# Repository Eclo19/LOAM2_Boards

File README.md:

# LOAM2_Boards_Winter/Spring_2026

## Description
These files contain the progress done on drone hardware for the LOAM 2 project. The current strategy is to produce a support board that connects to the Pixhawk's FMU, communicates with the nodes, and hosts many other vital systems. This board should concentrate as many of the drone peripherals as possible in a single PCB to ensure robustness. The support board contains the following sub-systems:

 * Power management and battery monitoring (PM)
 * GPS
 * ARM Switch
 * nRF54L15 (MCU)
 * nRF21540 (FEM)
 * GPS patch antenna
 * Bluetooth antenna (not certain yet)
 * JST Connectors for the FMU harness
 * Debug taps for all outputs

## Power Management

The power management issue is mostly solved. The board stored in `power_management_tests` was produced and thoroughly tested. We confirmed its outputs were the expected 3.3 and 5V, it handled the throuttle of the drone motors, and voltage and current readings are in agreement with lab equipment. **Note:** To ensure proper voltage and current readings, the resistor ratios implemented in the voltage and current sensors must be taken into account by the software. In Ardupilot, simply set `BATT_VOLT_MULT = 5.667` and `BATT_AMP_PERVLT = 25.0`. The chosen buck-converters can output currents of up to 3 A, far more than the FMU or the support board systems might draw. 

When redoing the layout for this board in the support board, make sure to follow IC datasheet recommendations and lay thick traces in the battery input and output ports, which can draw large currents (~80 A). 

## GPS

The GPS schematics were adapted from this repository: https://github.com/ZIOCC/Zio-Qwiic-GPS-Module-U-blox-NEO-M8N-0-10). They leverage the NEO-M8N-0 chip and a patch antenna at the GPS band of 1575.42 MHz. 

## Arm Switch

This replaces the floating ARM switch in the Pixhawk. 

## MCU and FEM

The drone communicates with node sensors through the nRF54L15 MCU using BLE. Currently, we assume the nodes will also host this MCU, as inter-communication between this IC is simple. The MCU is powered by the 3.3 V power line produced by the PM. Communication with the FMU is done through the TELEM2 port, which connects through UART to pins on the suppoart board MCU. 

The current drone wake-up strategy is to rely on energy harvesting to charge the base of an $npn$ transistor (2N3904) above its $V_{th}$, flipping the collector voltage from 3.3 V to 0 when charged, thus waking up the node. The node MCU must handle this and a few nuances regarding oscillation (described in our report) in firmware. We used the AEM30940 DK for our energy harvesting tests on the chosen band of 2.45 GHz. To ensure enough energy can be transmitted to charge the base of the transistor to around 0.65 V, a decent amount of power must be received. The The 47 C.F.R. § 15.247 permits a maximum of 1 W (30 dBm) of transmission power for the 2.45 GHz band given a few constraints, and the nRF54L15 can ony output a maximum of 8 dBm. To increase transmission power, we connect an RF FEM, the nRF21540, a bidirectional FEM (LNA for Rx and PA for Tx, with shiwtching controlled by GPIO pins or SPI). The antenna choice is still a major question for this transmission. 

The drone MCU in the suppoart board is programmed through an SWD interface. 

## Connectors and Debug Taps

The support board hosts multiple connectors that should be tightly packed in a harness connected to the FMU. These include the following ports: GPS, TELEM2, SWITCH, and POWER. Our initial connector selection was a DF13, but these are not fully compatible. We believe the correct connectors are JST. For testing and debugging reasons, it is helpful to pack debup taps for many essential nodes in the system (e.g. 3V3, 5V, CURRENT_SENSE, RX_GPS, etc). 

## Layout Notes

The layout of the support board has just started at the time of this README.md file. Like in the power management test board, the support board has DRCs from JLC PCB, imported from https://github.com/sethhillbrand/kicad_templates/tree/master. This board has 4 layers though, as opposed to the simple 2-layer power management tests board.

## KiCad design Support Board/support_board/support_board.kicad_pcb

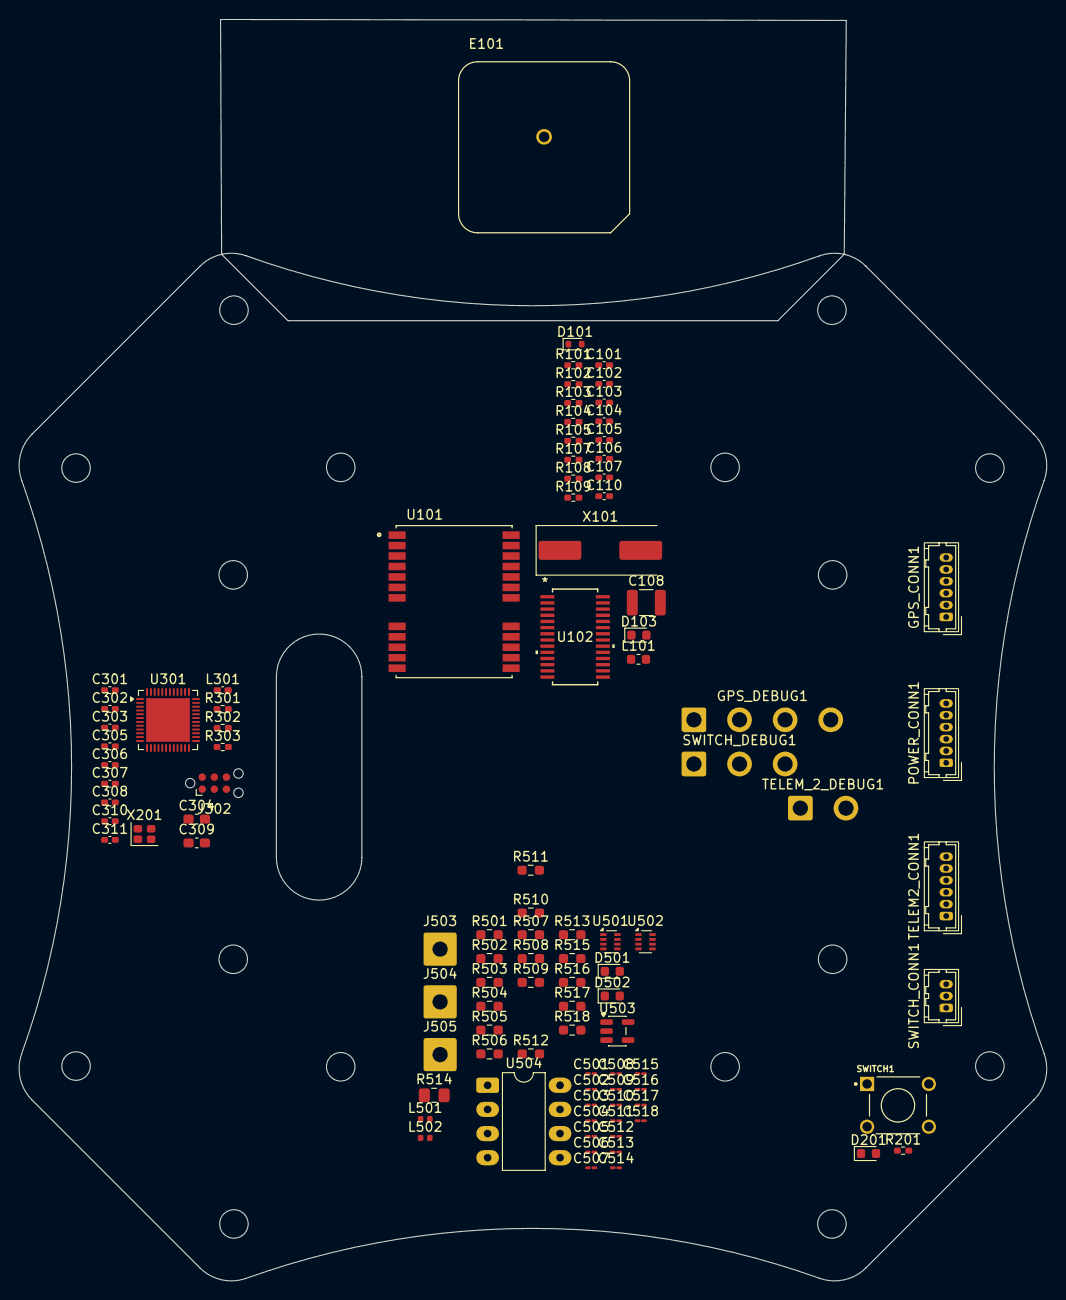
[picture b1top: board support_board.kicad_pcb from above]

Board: 4 copper layers, 108.1 x 132.7 mm, 100 parts (1 on the bottom side), 61 nets, no tracks yet.

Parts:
C101: 22pF ±10% 50V; C_0402_1005Metric_Pad0.74x0.62mm_HandSolder
C102: 33pF ±10% 50V; C_0402_1005Metric_Pad0.74x0.62mm_HandSolder
C103: 4.7uF ±10% 10V; C_0402_1005Metric_Pad0.74x0.62mm_HandSolder
C104, C105, C107, C110: 100nF ±10% 50V; C_0402_1005Metric_Pad0.74x0.62mm_HandSolder
C106: 10uF ±10% 10V; C_0402_1005Metric_Pad0.74x0.62mm_HandSolder
C108: XH414HG-IV01E; C_1210_3225Metric
C301, C302: 12pF; C_0402_1005Metric_Pad0.74x0.62mm_HandSolder
C303, C305, C306, C307, C308: 100nF; C_0402_1005Metric_Pad0.74x0.62mm_HandSolder
C304: 22 uF; C_0603_1608Metric_Pad1.08x0.95mm_HandSolder
C309: 0.3pF; C_0603_1608Metric_Pad1.08x0.95mm_HandSolder
C310: 0.5pF; C_0402_1005Metric_Pad0.74x0.62mm_HandSolder
C311: 10nF; C_0402_1005Metric_Pad0.74x0.62mm_HandSolder
C501, C502: 10 u; C_01005_0402Metric_Pad0.57x0.30mm_HandSolder
C503, C510, C516, C517: 100n; C_01005_0402Metric_Pad0.57x0.30mm_HandSolder
C504, C511: 22 n; C_01005_0402Metric_Pad0.57x0.30mm_HandSolder
C505, C512: 100 n; C_01005_0402Metric_Pad0.57x0.30mm_HandSolder
C506, C513: 22u; C_01005_0402Metric_Pad0.57x0.30mm_HandSolder
C507, C514: 22µ; C_01005_0402Metric_Pad0.57x0.30mm_HandSolder
C508: 470p; C_01005_0402Metric_Pad0.57x0.30mm_HandSolder
C509: 22 u; C_01005_0402Metric_Pad0.57x0.30mm_HandSolder
C515: 300p; C_01005_0402Metric_Pad0.57x0.30mm_HandSolder
C518: 1µ; C_01005_0402Metric_Pad0.57x0.30mm_HandSolder
D101: RB520S30T1G; D_SOD-523
D103: GREEN; LED_0603_1608Metric
D201, D501: RED; LED_0603_1608Metric
D502: YELLOW; LED_0603_1608Metric
E101: APAE1575R1820ABDC1-T; XDCR_APAE1575R1820ABDC1-T
GPS_CONN1: Conn_01x06_Socket; Hirose_DF13-06P-1.25DSA_1x06_P1.25mm_Vertical
GPS_DEBUG1: Conn_01x04_Socket; SolderWire-0.75sqmm_1x04_P4.8mm_D1.25mm_OD2.3mm
J301: Conn_Coaxial; U.FL_Hirose_U.FL-R-SMT-1_Vertical
J302: Conn_ARM_SWD_TagConnect_TC2030-NL; Tag-Connect_TC2030-IDC-NL_2x03_P1.27mm_Vertical
J503, J504, J505: Conn_01x01_Socket; SolderWire-0.75sqmm_1x01_D1.25mm_OD3.5mm
L101: 22uH ±10%; L_0603_1608Metric
L301: 2nH; L_0402_1005Metric_Pad0.77x0.64mm_HandSolder
L501, L502: 6.8µH; L_0402_1005Metric
POWER_CONN1: Conn_01x06_Socket; Hirose_DF13-06P-1.25DSA_1x06_P1.25mm_Vertical
R101, R107, R109: 1K ±1%; R_0402_1005Metric_Pad0.72x0.64mm_HandSolder
R102, R103: 10K ±1%; R_0402_1005Metric_Pad0.72x0.64mm_HandSolder
R104, R105: 4.7K ±1%; R_0402_1005Metric_Pad0.72x0.64mm_HandSolder
R108: 22R ±1%; R_0402_1005Metric_Pad0.72x0.64mm_HandSolder
R201: 220; R_0402_1005Metric_Pad0.72x0.64mm_HandSolder
R301: 10k; R_0402_1005Metric_Pad0.72x0.64mm_HandSolder
R302, R303: 100; R_0402_1005Metric_Pad0.72x0.64mm_HandSolder
R501, R507: 191k; R_0603_1608Metric_Pad0.98x0.95mm_HandSolder
R502, R508: 49.9k; R_0603_1608Metric_Pad0.98x0.95mm_HandSolder
R503: 100k; R_0603_1608Metric_Pad0.98x0.95mm_HandSolder
R504, R509, R510, R511, R516: 10k; R_0603_1608Metric_Pad0.98x0.95mm_HandSolder
R505: 9.09k; R_0603_1608Metric_Pad0.98x0.95mm_HandSolder
R506: 51k; R_0603_1608Metric_Pad0.98x0.95mm_HandSolder
R512: 90.9k; R_0603_1608Metric_Pad0.98x0.95mm_HandSolder
R513: 56k; R_0603_1608Metric_Pad0.98x0.95mm_HandSolder
R514: 12k; C_0805_2012Metric_Pad1.18x1.45mm_HandSolder
R515: 4m; R_0603_1608Metric_Pad0.98x0.95mm_HandSolder
R517, R518: 1K ±1%; R_0603_1608Metric_Pad0.98x0.95mm_HandSolder
SWITCH1: 1825910-6; SW_1825910-6-4
SWITCH_CONN1: Conn_01x03_Socket; Hirose_DF13-03P-1.25DSA_1x03_P1.25mm_Vertical
SWITCH_DEBUG1: Conn_01x03_Socket; SolderWire-0.75sqmm_1x03_P4.8mm_D1.25mm_OD2.3mm
TELEM2_CONN1: Conn_01x06_Socket; Hirose_DF13-06P-1.25DSA_1x06_P1.25mm_Vertical
TELEM_2_DEBUG1: Conn_01x02_Socket; SolderWire-0.75sqmm_1x02_P4.8mm_D1.25mm_OD2.3mm
U101: NEO-M8N; NEO-M8N-0
U102: SC16IS752
U301: nRF54L15-QFXX; QFN-48-1EP_6x6mm_P0.4mm_EP4.6x4.6mm
U501, U502: MP2338; SOT-583-8
U503: INA169; SOT-23-5
U504: MCP6002T-E/OT; DIP-8_W7.62mm_LongPads
X101: 3.072MHZ; Crystal_SMD_HC49-SD
X201: Crystal_GND24; Crystal_SMD_2016-4Pin_2.0x1.6mm

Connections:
3V3: C105.2, C106.2, C107.2, C110.2, C303.1, C304.1, C506.1, C507.1, C508.2, C516.1, C517.1, C518.1, J302.1 (VCC), L501.2, R101.2, R102.2, R103.2, R104.2, R105.2, R301.1, R503.2, R506.2, R518.2, U101.7 (VDD_USB), U101.23 (VCC), U102.8 (VDD), U301.10 (VDD), U301.22 (VDD), U301.36 (VDD), U301.47 (VDD), U301.48 (VDD), U503.5 (V+), U504.8 (V+)
5V: C513.1, C514.1, C515.2, L502.2, R509.2, R512.2, R517.2
/GPS/IRQ: R101.1, U102.15 (~IRQ)
/GPS/RESET: R103.1, U102.5 (~RESET)
/GPS/RXD_GPS: U101.21 (RXD), U102.3 (TXA)
/GPS/TXD_GPS: U101.20 (TXD), U102.4 (RXA)
/connectors/5V: POWER_CONN1.1, POWER_CONN1.2
/connectors/GND: GPS_CONN1.5, POWER_CONN1.5, POWER_CONN1.6, TELEM2_CONN1.6
/connectors/RXD_GPS: GPS_CONN1.3, GPS_DEBUG1.3
/connectors/RXD_TELEM2: TELEM2_CONN1.3, TELEM_2_DEBUG1.2
/connectors/SWITCH_LED: SWITCH_CONN1.2, SWITCH_DEBUG1.3
/connectors/SWITCH_OUT: SWITCH_CONN1.3, SWITCH_DEBUG1.2
/connectors/SWITCH_VCC: SWITCH_CONN1.1, SWITCH_DEBUG1.1
/connectors/TXD_GPS: GPS_CONN1.4, GPS_DEBUG1.4
/connectors/TXD_TELEM2: TELEM2_CONN1.2, TELEM_2_DEBUG1.1
/power/CURRENT_SENSE: J504.1, U504.6 (-), U504.7
/power/VOLTAGE_SENSE: J503.1, U504.1, U504.2 (-)
/power/V_bat: C501.1, C502.1, C503.1, C509.1, C510.1, R501.1, R507.1, R515.2, U501.2 (VIN), U502.2 (VIN), U503.4 (-)
/power/V_bat_in: R513.1, R515.1, U503.3 (+)
GND: C101.1, C102.1, C103.1, C104.1, C105.1, C106.1, C107.1, C110.1, C301.2, C302.1, C303.2, C304.2, C305.2, C306.2, C307.2, C308.2, C309.2, C310.2, C311.1, C501.2, C502.2, C503.2, C504.2, C506.2, C507.2, C509.2, C510.2, C511.2, C513.2, C514.2, C516.2, C517.2, C518.2, J301.2 (Ext), J302.5 (GND), J505.1, R502.2, R505.1, R508.2, R511.1, R514.2, R516.2, U101.10 (GND@1), U101.12 (GND@2), U101.13 (GND@3), U101.24 (GND@4), U102.10 (A0), U102.11 (A1), U102.22 (VSS), U301.32 (VSS_PA), U301.44 (VSS), U301.49 (VSS), U501.4 (GND), U502.4 (GND), U503.2 (GND), U504.4 (V-), X201.2 (G), X201.4 (G)
unnamed: C508.1, R504.2, R505.2, R506.1
unnamed: C515.1, R510.2, R511.2, R512.1
unnamed: D201.1 (K), R201.1
unnamed: C309.1, C310.1, J301.1 (In), L301.2
unnamed: J302.4 (SWCLK), R302.2
unnamed: J302.2 (SWDIO), R303.2
unnamed: C311.2, J302.3 (~RESET), R301.2, U301.30 (~RESET)
unnamed: L101.1, R108.2
unnamed: R108.1, U101.8 (REST_N), U101.9 (VCC_RF)
unnamed: E101.1, L101.2, U101.11 (RF_IN)
unnamed: R107.2, U101.3 (TIMEPULSE)
unnamed: C103.2, C104.2, R109.2, U101.22 (V_BCKP)
unnamed: R102.1, U102.9 (I2C)
unnamed: C101.2, U102.6 (XTAL1), X101.2
unnamed: C102.2, U102.7 (XTAL2), X101.1
unnamed: L301.1, U301.31 (ANT)
unnamed: C308.1, U301.46 (DCC)
unnamed: C305.1, U301.43 (DECA)
unnamed: C307.1, U301.45 (DECD)
unnamed: C306.1, U301.33 (DECRF)
unnamed: R302.1, U301.26 (SWDCLK)
unnamed: R303.1, U301.25 (SWDIO)
unnamed: C302.2, U301.34 (XC1), X201.1
unnamed: C301.1, U301.35 (XC2), X201.3
unnamed: C505.1, U501.5 (BST)
unnamed: R501.2, R502.1, U501.6 (EN)
unnamed: R504.1, U501.8 (FB)
unnamed: R503.1, U501.1 (PG)
unnamed: C504.1, U501.7 (SS)
unnamed: C505.2, L501.1, U501.3 (SW)
unnamed: C512.1, U502.5 (BST)
unnamed: R507.2, R508.1, U502.6 (EN)
unnamed: R510.1, U502.8 (FB)
unnamed: R509.1, U502.1 (PG)
unnamed: C511.1, U502.7 (SS)
unnamed: C512.2, L502.1, U502.3 (SW)
unnamed: R513.2, R514.1, U504.3 (+)
unnamed: R516.1, U503.1, U504.5 (+)
SCL: GPS_CONN1.1, GPS_DEBUG1.1, R104.1, U102.13 (SCL)
SDA: GPS_CONN1.2, GPS_DEBUG1.2, R105.1, U102.14 (SDA)
SWITCH_VCC: D201.2 (A), SWITCH1.1

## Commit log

2026-05-01 Add initial README.md for LOAM2_Boards
2026-05-01 FIrst Commit: PM Test Board
2026-05-01 Added BOM
2026-05-04 Updated BOM and fixed minor mismatches
2026-05-07 Final Check
2026-05-30 Added Current Support
    Added nRF ICs.
2026-06-02 Updated PM files and Schematics in the Support Board
2026-06-05 Added edited README
    .
2026-06-05 Add layout notes for support board design
